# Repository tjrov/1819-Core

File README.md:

# 1819-Core
All software and hardware for 2018-19 season

## Software
### ControlStation
If you want to program something, the ControlStation is a great place to start.

So far, I've made abstract classes for sub-Panels of the GUI that control robot actuators
or read data from robot sensors. Serial comms are already taken care of. Just instantiate
one of the concrete subclasses and add it to the GUI controls.

The UpdateControls() methods are what draws the UI for each Device class. This method will run after the device is updated over serial.
New information will be available in the Data field of the class, and you can update the UI with that data.

TODO:
- Make UI look better (probably have the controls take up more of the screen and be laid out less haphazardly. Also maybe use win10 look and feel)
- Controller input
- Heading lock (override handheld controller values and control motors based on heading as compared to a desired heading)
- Depth lock
- Roll lock

It's recommended to use Visual Studio with the .NET and Windows Forms stuff installed for 
ControlStation development.

### autopilot-firmware

The autopilot-firmware and motorcontroller-firmware code is pretty much done. For development of firmware for the autopilot and motorcontroller, which are Arduino boards, install the Visual Micro plugin for Visual Studio. Upload the autopilot-firmware to a regular Arduino board connected to your computer over USB (comment out code that actually uses sensors and actuators since it won't work anyway), then start the ControlStation code and test out the UI.

### Uploading procedure

It's kinda complicated since we only have RS-485 (one twisted pair of wires) connecting the surface and ROV computers
1. You click upload in visual studio on the surface computer
2. The code gets compiled into a .hex file
3. The board.txt file (in the project directory) specifies a pre-upload command to run reset.bat (also in that directory)
4. reset.bat sends a command to the ROV: (hex) 42 83 01 03 02
5. On receiving this command, the autopilot-firmware (as well as the autopilot-setup code once it has finished running) will jump to the start of its bootloader code
6. reset.bat runs avrdude to upload the .hex file to the ROV

## Hardware

Electronics people can take a look at the autopilot board files. We'll also be making a
motorcontroller board that connects to the ROV's i2c bus. You can use Eagle with the Sparkfun Eagle part libraries installed to work on them.

Current autopilot revision features:
- Arduino Pro Mini
- RGB status LED
- RS485 interface
- Auto direction control of rs485 interface allows new firmware to be uploaded over the tether
- PCA-9615 differential I2C transceiver allows it to talk to the ROV data bus and access the motorcontroller board and the 6 ESC boards
- I2C Orientation sensor gives compass heading, pitch, and roll angles
- I2C Pressure sensor provides a depth reading

Motorcontroller current features:
- Arduino Pro Mini
- RGB status led
- PCA-9615 differential I2C transceiver (connects to the ROV i2c bus)
See the autopilot board schematic for how to wire the I2C circuits, since they
are the same on that board.
- Bus termination (see autopilot board schematic)
- 3x DRV8871 motor drivers. (wired as they are on the adafruit breakouts)

Motorcontroller planned additional features (need to be drawn in schematic and board files):
- I2C device that can generate PWM control signals for at least six ESCs (PCA-9685, perhaps)
- MOSFET switches (1-2Amp, at least 2 or 3 of them) controlled by these PWM signals

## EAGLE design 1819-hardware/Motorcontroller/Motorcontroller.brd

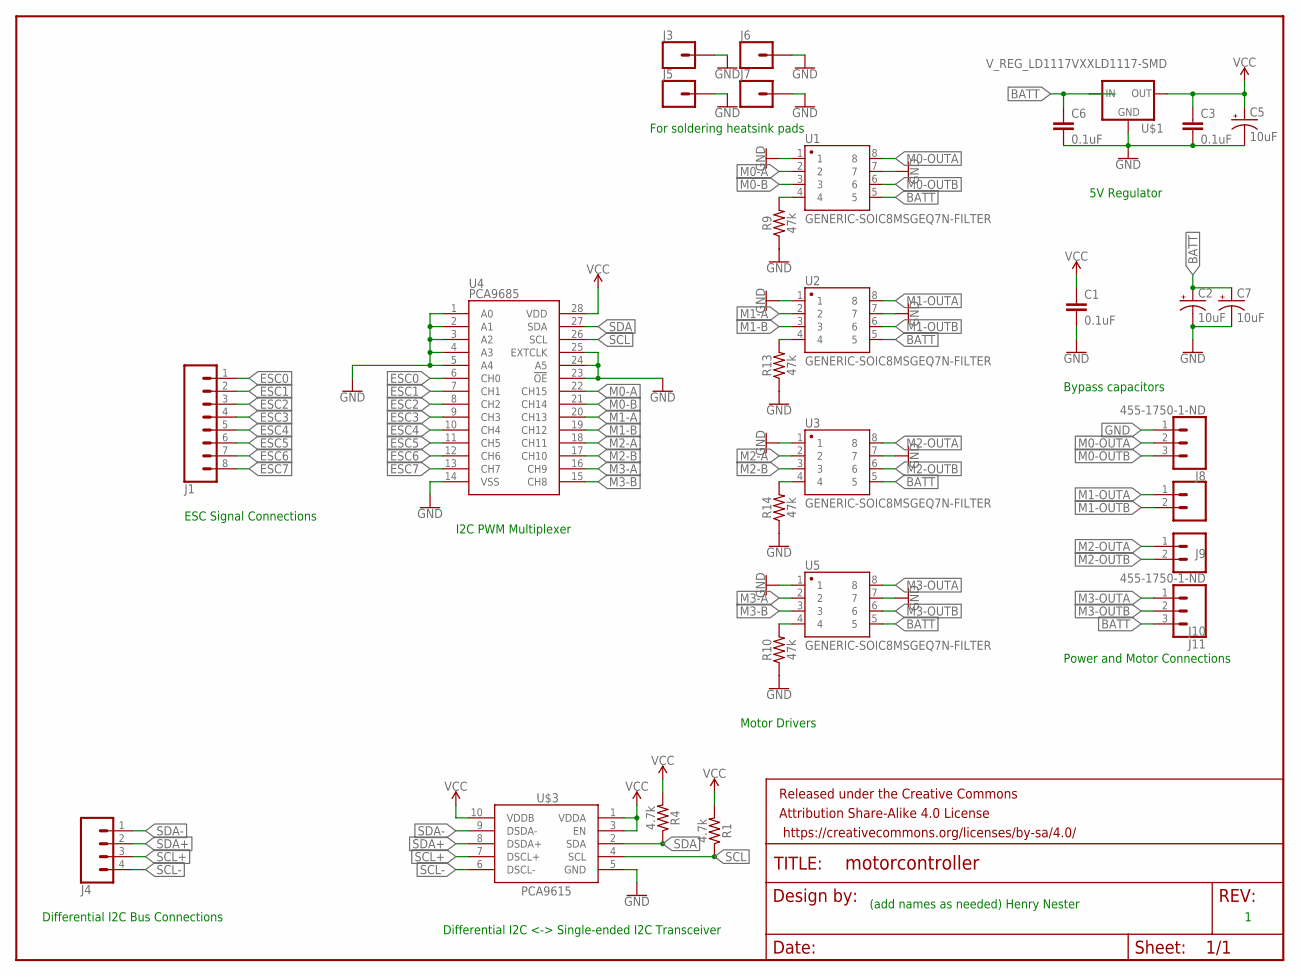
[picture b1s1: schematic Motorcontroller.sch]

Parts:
C1, C3, C6: 0.1uF; 0603
C2, C5, C7: 10uF; CPOL-RADIAL-2.5MM-5MM
FRAME1: FRAME-LETTERNO_PACKAGE; DUMMY
J1: CONN_08"; 1X08
J3, J5, J6, J7: CONN_01PTH_NO_SILK_YES_STOP; 1X01_NO_SILK
J4: CONN_04; 1X04
J8, J11: 455-1750-1-ND; 1X03
J9, J10: CONN_02; 1X02
R1, R4: 4.7k; 0603
R9, R10, R13, R14: 47k; 0603
U1, U2, U3, U5: GENERIC-SOIC8MSGEQ7N-FILTER; SO08
U4: PCA9685; TSSOP-28_4MM
U$1: V_REG_LD1117VXXLD1117-SMD; SOT223
U$3: PCA9615; TSSOP10

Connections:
BATT: C2.1 (+), C6.1, C7.1 (+), J11.3, U1.5, U2.5, U3.5, U5.5, U$1.3 (IN)
ESC0: J1.1, U4.6 (CH0)
ESC1: J1.2, U4.7 (CH1)
ESC2: J1.3, U4.8 (CH2)
ESC3: J1.4, U4.9 (CH3)
ESC4: J1.5, U4.10 (CH4)
ESC5: J1.6, U4.11 (CH5)
ESC6: J1.7, U4.12 (CH6)
ESC7: J1.8, U4.13 (CH7)
GND: C1.2, C2.2 (-), C3.2, C5.2 (-), C6.2, C7.2 (-), J3.1, J5.1, J6.1, J7.1, J8.1, R9.1, R10.1, R13.1, R14.1, U1.1, U1.7, U2.1, U2.7, U3.1, U3.7, U4.1 (A0), U4.2 (A1), U4.3 (A2), U4.4 (A3), U4.5 (A4), U4.14 (VSS), U4.23 (!OE), U4.24 (A5), U4.25 (EXTCLK), U5.1, U5.7, U$1.1 (GND), U$3.5 (GND)
M0-A: U1.2, U4.22 (CH15)
M0-B: U1.3, U4.21 (CH14)
M0-OUTA: J8.2, U1.8
M0-OUTB: J8.3, U1.6
M1-A: U2.2, U4.20 (CH13)
M1-B: U2.3, U4.19 (CH12)
M1-OUTA: J9.1, U2.8
M1-OUTB: J9.2, U2.6
M2-A: U3.2, U4.18 (CH11)
M2-B: U3.3, U4.17 (CH10)
M2-OUTA: J10.1, U3.8
M2-OUTB: J10.2, U3.6
M3-A: U4.16 (CH9), U5.2
M3-B: U4.15 (CH8), U5.3
M3-OUTA: J11.1, U5.8
M3-OUTB: J11.2, U5.6
unnamed: R13.2, U2.4
unnamed: R14.2, U3.4
unnamed: R10.2, U5.4
unnamed: R9.2, U1.4
SCL: R1.1, U4.26 (SCL), U$3.4 (SCL)
SCL+: J4.3, U$3.7 (DSCL+)
SCL-: J4.4, U$3.6 (DSCL-)
SDA: R4.1, U4.27 (SDA), U$3.2 (SDA)
SDA+: J4.2, U$3.8 (DSDA+)
SDA-: J4.1, U$3.9 (DSDA-)
VCC: C1.1, C3.1, C5.1 (+), R1.2, R4.2, U4.28 (VDD), U$1.2 (OUT), U$3.1 (VDDA), U$3.3 (EN), U$3.10 (VDDB)

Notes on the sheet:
(add names as needed) Henry Nester
5V Regulator
Power and Motor Connections
Bypass capacitors
I2C PWM Multiplexer
Motor Drivers
ESC Signal Connections
Differential I2C <-> Single-ended I2C Transceiver
Differential I2C Bus Connections
For soldering heatsink pads

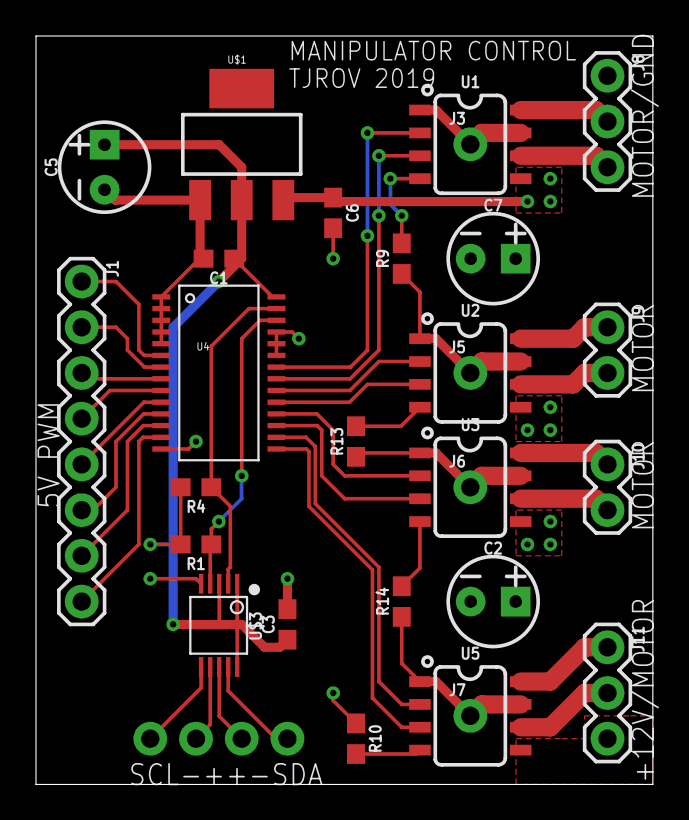
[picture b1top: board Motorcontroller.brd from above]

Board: 2 copper layers, 34.3 x 41.6 mm, 30 parts (1 on the bottom side), 37 nets.

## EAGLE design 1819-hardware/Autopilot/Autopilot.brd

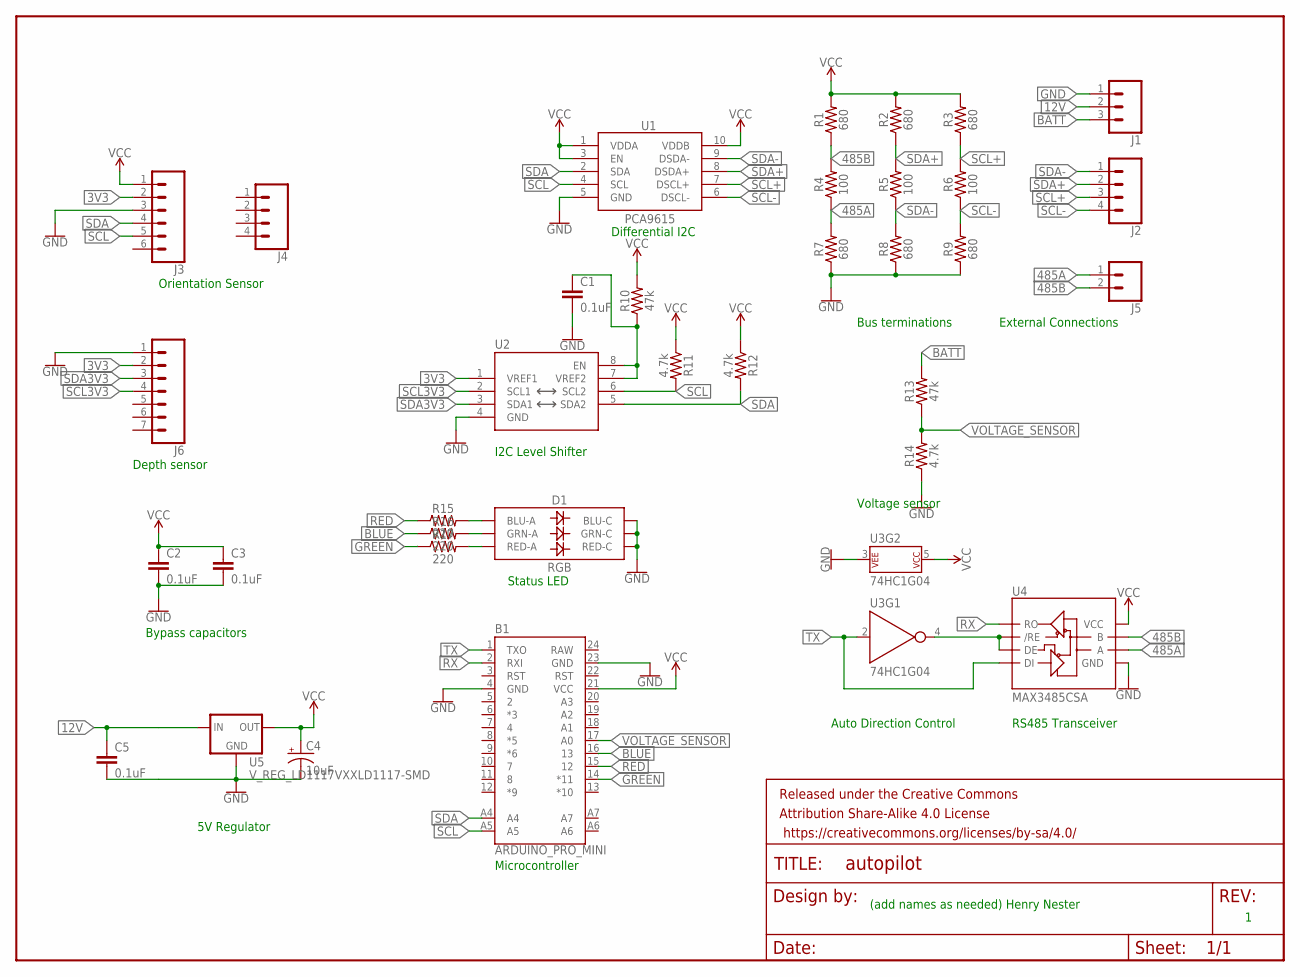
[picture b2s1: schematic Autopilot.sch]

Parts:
B1: ARDUINO_PRO_MINI
C1, C2, C3, C5: 0.1uF; 0603
C4: 10uF; CPOL-RADIAL-2.5MM-5MM
D1: RGB; PLCC-6-LED
FRAME1: FRAME-LETTERNO_PACKAGE; DUMMY
J1: CONN_03LONGPADS; 1X03_LONGPADS
J2: CONN_04; 1X04
J3: CONN_06NO_SILK_FEMALE_PTH; 1X06_NO_SILK
J4: CONN_041X04_NO_SILK; 1X04_NO_SILK
J5: CONN_02; 1X02
J6: CONN_07NO_SILK; 1X07_NO_SILK
R1, R2, R3, R7, R8, R9: 680; 0603
R4, R5, R6: 100; 0603
R10, R13: 47k; 0603
R11, R12, R14: 4.7k; 0603
R15, R16, R17: 220; 0603
U1: PCA9615; TSSOP10
U2: PCA9306MSOP-8; MSOP8
U3: 74HC1G04; SOT353
U4: MAX3485CSA; SO08
U5: V_REG_LD1117VXXLD1117-SMD; SOT223

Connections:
3V3: J3.2, J6.2, U2.1 (VREF1)
12V: C5.1, J1.2, U5.3 (IN)
485A: J5.1, R4.1, R7.2, U4.6 (A)
485B: J5.2, R1.1, R4.2, U4.7 (B)
BATT: J1.3, R13.2
BLUE: B1.16 (13), R16.1
GND: B1.4 (GND), B1.23 (GND), C1.2, C2.2, C3.2, C4.2 (-), C5.2, D1.CB (BLU-C), D1.CG (GRN-C), D1.CR (RED-C), J1.1, J3.3, J6.1, R7.1, R8.1, R9.1, R14.1, U1.5 (GND), U2.4 (GND), U3.3 (P$V-), U4.5 (GND), U5.1 (GND)
GREEN: B1.14 (*11), R17.1
unnamed: U3.4 (Y), U4.2 (/RE), U4.3 (DE)
unnamed: D1.AB (BLU-A), R15.2
unnamed: D1.AG (GRN-A), R16.2
unnamed: D1.AR (RED-A), R17.2
unnamed: C1.1, R10.1, U2.7 (VREF2), U2.8 (EN)
RAW: B1.24 (RAW)
RED: B1.15 (12), R15.1
RX: B1.2 (RXI), U4.1 (RO)
SCL: B1.A5, J3.5, R11.2, U1.4 (SCL), U2.6 (SCL2)
SCL3V3: J6.4, U2.2 (SCL1)
SCL+: J2.3, R3.1, R6.2, U1.7 (DSCL+)
SCL-: J2.4, R6.1, R9.2, U1.6 (DSCL-)
SDA: B1.A4, J3.4, R12.2, U1.2 (SDA), U2.5 (SDA2)
SDA3V3: J6.3, U2.3 (SDA1)
SDA+: J2.2, R2.1, R5.2, U1.8 (DSDA+)
SDA-: J2.1, R5.1, R8.2, U1.9 (DSDA-)
TX: B1.1 (TXO), U3.2 (A), U4.4 (DI)
VCC: B1.21 (VCC), C2.1, C3.1, C4.1 (+), J3.1, R1.2, R2.2, R3.2, R10.2, R11.1, R12.1, U1.1 (VDDA), U1.3 (EN), U1.10 (VDDB), U3.5 (P$V+), U4.8 (VCC), U5.2 (OUT)
VOLTAGE_SENSOR: B1.17 (A0), R13.1, R14.2

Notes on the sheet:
(add names as needed) Henry Nester
Orientation Sensor
Differential I2C
I2C Level Shifter
RS485 Transceiver
Auto Direction Control
5V Regulator
Microcontroller
External Connections
Status LED
Bus terminations
Bypass capacitors
Voltage sensor
Depth sensor

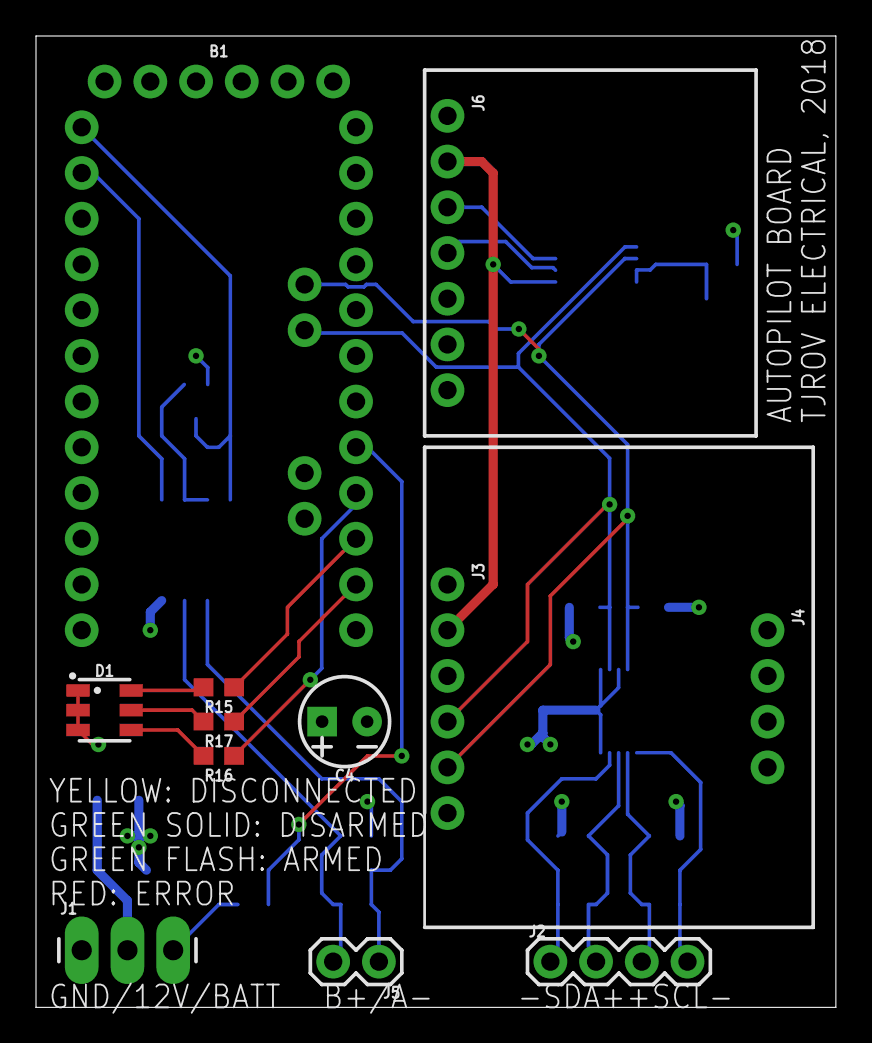
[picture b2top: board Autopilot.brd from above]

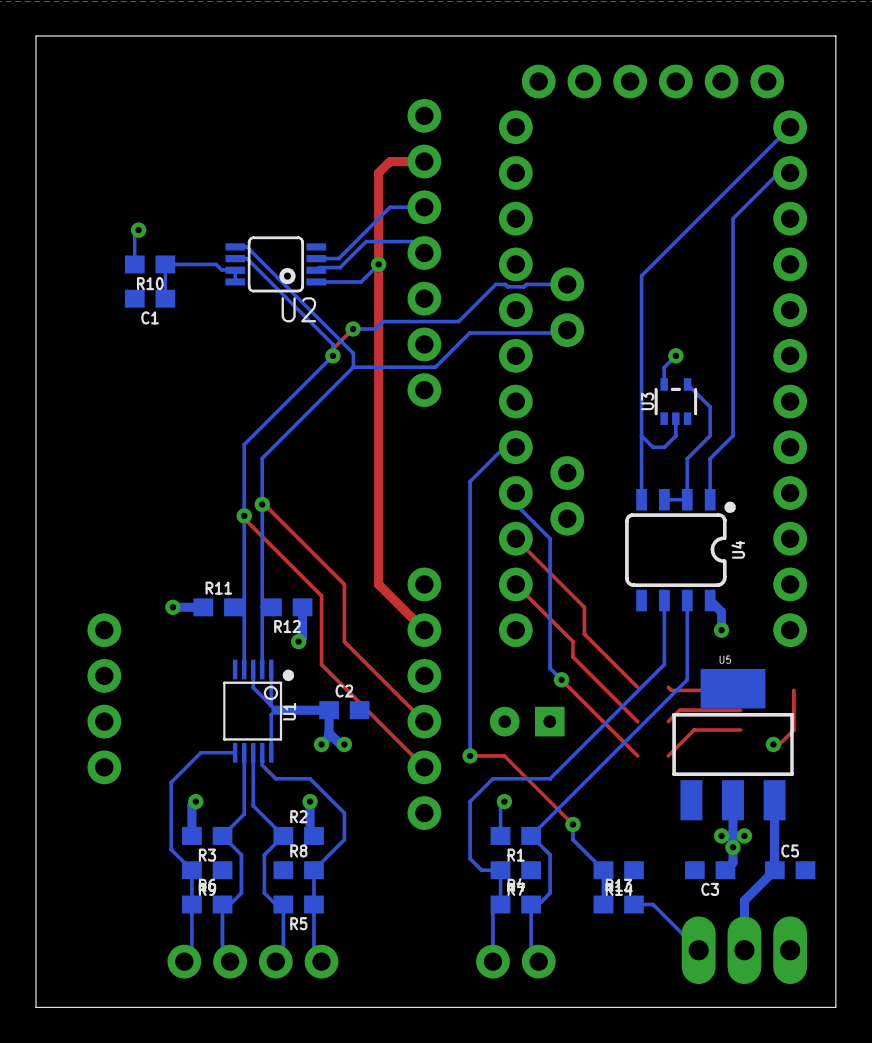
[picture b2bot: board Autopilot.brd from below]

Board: 2 copper layers, 44.4 x 54.0 mm, 36 parts (23 on the bottom side), 26 nets.

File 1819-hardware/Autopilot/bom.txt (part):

Partlist exported from C:/Users/Henry/source/repos/1819-Core/1819-hardware/Autopilot/Autopilot.sch at 9/2/2018 9:28 AM

Part   Value                     Device                          Package               Description                                                                                                     DESIGNER PROD_ID    VALUE       VERSION
B1     ARDUINO_PRO_MINI          ARDUINO_PRO_MINI                ARDUINO_PRO_MINI      SparkFun Pro Mini                                                                                                                                      
C1     0.1uF                     0.1UF-0603-25V-(+80/-20%)       0603                  0.1µF ceramic capacitors                                                                                                 CAP-00810  0.1uF              
C2     0.1uF                     0.1UF-0603-25V-(+80/-20%)       0603                  0.1µF ceramic capacitors                                                                                                 CAP-00810  0.1uF              
C3     0.1uF                     0.1UF-0603-25V-(+80/-20%)       0603                  0.1µF ceramic capacitors                                                                                                 CAP-00810  0.1uF              
C4     10uF                      10UF-POLAR-RADIAL-2.5MM-25V-20% CPOL-RADIAL-2.5MM-5MM 10.0µF polarized capacitors                                                                                              CAP-08440  10uF               
C5     0.1uF                     0.1UF-0603-25V-(+80/-20%)       0603                  0.1µF ceramic capacitors                                                                                                 CAP-00810  0.1uF              
D1     RGB                       LED-RGBPLCC-6                   PLCC-6-LED            LED-RGB                                                                                                                  DIO-12113  RGB                
FRAME1 FRAME-LETTERNO_PACKAGE    FRAME-LETTERNO_PACKAGE          DUMMY                 Schematic Frame - Letter                                                                                        Nobody                          v01    
J1                               CONN_03LONGPADS                 1X03_LONGPADS         Multi connection point. Often used as Generic Header-pin footprint for 0.1 inch spaced/style header connections                                        
J2                               CONN_04                         1X04                  Multi connection point. Often used as Generic Header-pin footprint for 0.1 inch spaced/style header connections          CONN-09696                    
J3                               CONN_06NO_SILK_FEMALE_PTH       1X06_NO_SILK          Multi connection point. Often used as Generic Header-pin footprint for 0.1 inch spaced/style header connections          CONN-08437                    
J4                               CONN_041X04_NO_SILK             1X04_NO_SILK          Multi connection point. Often used as Generic Header-pin footprint for 0.1 inch spaced/style header connections          CONN-09696                    
J5                               CONN_02                         1X02                  Multi connection point. Often used as Generic Header-pin footprint for 0.1 inch spaced/style header connections                                        
J6                               CONN_07NO_SILK                  1X07_NO_SILK          Multi connection point. Often used as Generic Header-pin footprint for 0.1 inch spaced/style header connections                                        
R1     680                       680OHM-0603-1/10W-5%            0603                  680Ω resistor                                                                                                            RES-09333  680                
R2     680                       680OHM-0603-1/10W-5%            0603                  680Ω resistor                                                                                                            RES-09333  680                
R3     680                       680OHM-0603-1/10W-5%            0603                  680Ω resistor                                                                                                            RES-09333  680                
R4     100                       100OHM-0603-1/4W-5%             0603                  100Ω resistor                                                                                                            RES-12438  100                
R5     100                       100OHM-0603-1/4W-5%             0603                  100Ω resistor                                                                                                            RES-12438  100                
R6     100                       100OHM-0603-1/4W-5%             0603                  100Ω resistor                                                                                                            RES-12438  100                
R7     680                       680OHM-0603-1/10W-5%            0603                  680Ω resistor                                                                                                            RES-09333  680                
R8     680                       680OHM-0603-1/10W-5%            0603                  680Ω resistor                                                                                                            RES-09333  680                
R9     680                       680OHM-0603-1/10W-5%            0603                  680Ω resistor                                                                                                            RES-09333  680                
R10    47k                       100KOHM-0603-1/10W-1%           0603                  100kΩ resistor                                                                                                           RES-07828  100k               
R11    4.7k                      4.7KOHM-0603-1/10W-1%           0603                  4.7kΩ resistor                                                                                                           RES-07857  4.7k               
R12    4.7k                      4.7KOHM-0603-1/10W-1%           0603                  4.7kΩ resistor                                                                                                           RES-07857  4.7k               
R13    47k                       100KOHM-0603-1/10W-1%           0603                  100kΩ resistor                                                                                                           RES-07828  100k               
R14    4.7k                      4.7KOHM-0603-1/10W-1%           0603                  4.7kΩ resistor                                                                                                           RES-07857  4.7k               
R15    220                       220OHM-0603-1/10W-1%            0603                  220Ω resistor                                                                                                            RES-07861  220                
R16    220                       220OHM-0603-1/10W-1%            0603                  220Ω resistor                                                                                                            RES-07861  220                
R17    220                       220OHM-0603-1/10W-1%            0603                  220Ω resistor                                                                                                            RES-07861  220                
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
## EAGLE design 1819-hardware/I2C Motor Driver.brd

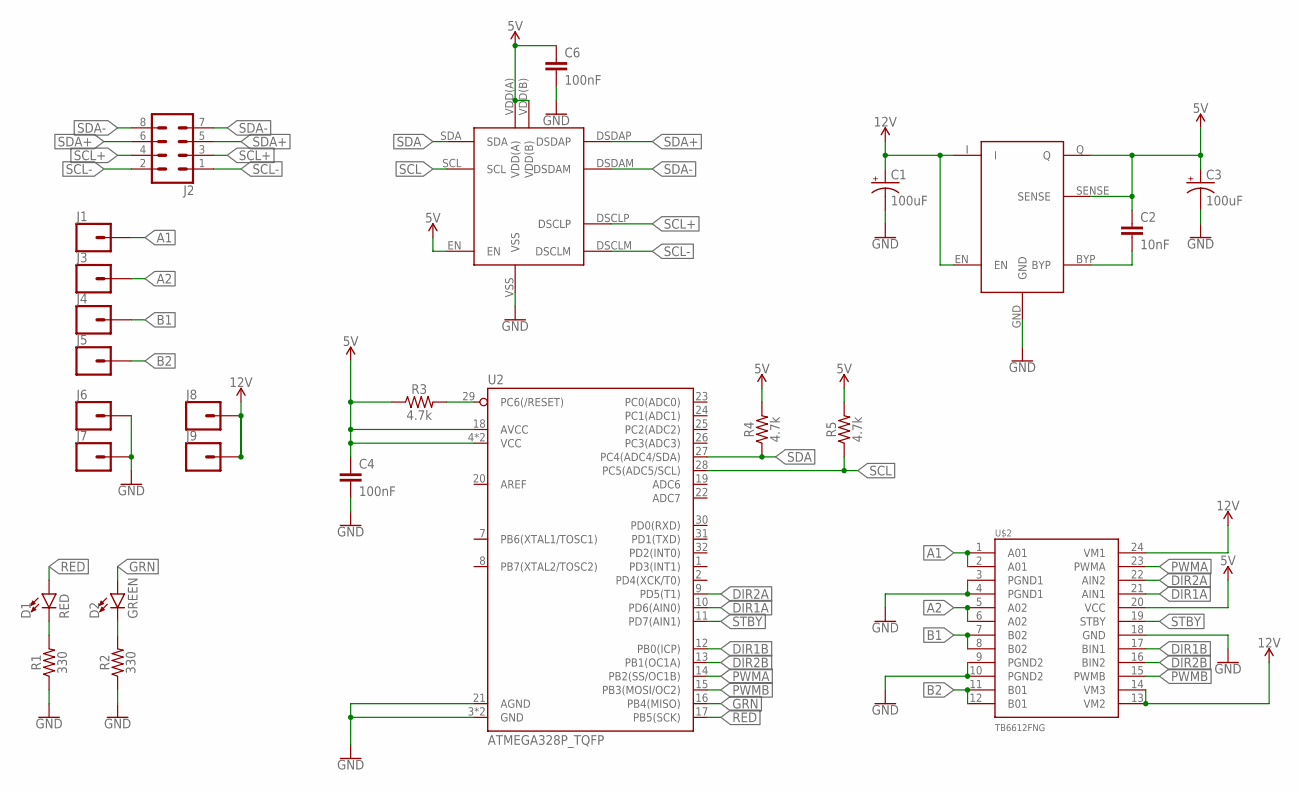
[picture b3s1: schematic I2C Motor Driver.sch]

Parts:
C1, C3: 100uF; CPOL-RADIAL-2.5MM-6.5MM
C2: 10nF; 0603
C4, C6: 100nF; 0603
D1: RED; LED-0603
D2: GREEN; LED-0603
J1, J3, J4, J5, J6, J7, J8, J9: CONN_01PTH_2MM; 1X01_2MM
J2: CONN_04X2; 2X4
R1, R2: 330; 0603
R3, R4, R5: 4.7k; 0603
U1: TLS205B0
U2: ATMEGA328P_TQFP; TQFP32-08
U$1: PCA9615
U$2: TB6612FNG; SSOP24

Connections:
5V: C2.1, C3.1 (+), C4.1, C6.1, R3.1, R4.2, R5.2, U1.Q, U1.SENSE, U2.4 (VCC), U2.6 (VCC), U2.18 (AVCC), U$1.EN, U$1.VDD(A), U$1.VDD(B), U$2.20 (VCC)
12V: C1.1 (+), J8.1, J9.1, U1.EN, U1.I, U$2.13 (VM2), U$2.14 (VM3), U$2.24 (VM1)
A1: J1.1, U$2.1 (A01), U$2.2 (A01)
A2: J3.1, U$2.5 (A02), U$2.6 (A02)
B1: J4.1, U$2.7 (B02), U$2.8 (B02)
B2: J5.1, U$2.11 (B01), U$2.12 (B01)
DIR1A: U2.10 (PD6(AIN0)), U$2.21 (AIN1)
DIR1B: U2.12 (PB0(ICP)), U$2.17 (BIN1)
DIR2A: U2.9 (PD5(T1)), U$2.22 (AIN2)
DIR2B: U2.13 (PB1(OC1A)), U$2.16 (BIN2)
GND: C1.2 (-), C3.2 (-), C4.2, C6.2, J6.1, J7.1, R1.1, R2.1, U1.GND, U2.3 (GND), U2.5 (GND), U2.21 (AGND), U$1.VSS, U$2.3 (PGND1), U$2.4 (PGND1), U$2.9 (PGND2), U$2.10 (PGND2), U$2.18 (GND)
GRN: D2.A, U2.16 (PB4(MISO))
unnamed: C2.2, U1.BYP
unnamed: D2.C, R2.2
unnamed: D1.C, R1.2
unnamed: R3.2, U2.29 (PC6(/RESET))
PWMA: U2.14 (PB2(SS/OC1B)), U$2.23 (PWMA)
PWMB: U2.15 (PB3(MOSI/OC2)), U$2.15 (PWMB)
RED: D1.A, U2.17 (PB5(SCK))
SCL: R5.1, U2.28 (PC5(ADC5/SCL)), U$1.SCL
SCL+: J2.3, J2.4, U$1.DSCLP
SCL-: J2.1, J2.2, U$1.DSCLM
SDA: R4.1, U2.27 (PC4(ADC4/SDA)), U$1.SDA
SDA+: J2.5, J2.6, U$1.DSDAP
SDA-: J2.7, J2.8, U$1.DSDAM
STBY: U2.11 (PD7(AIN1)), U$2.19 (STBY)

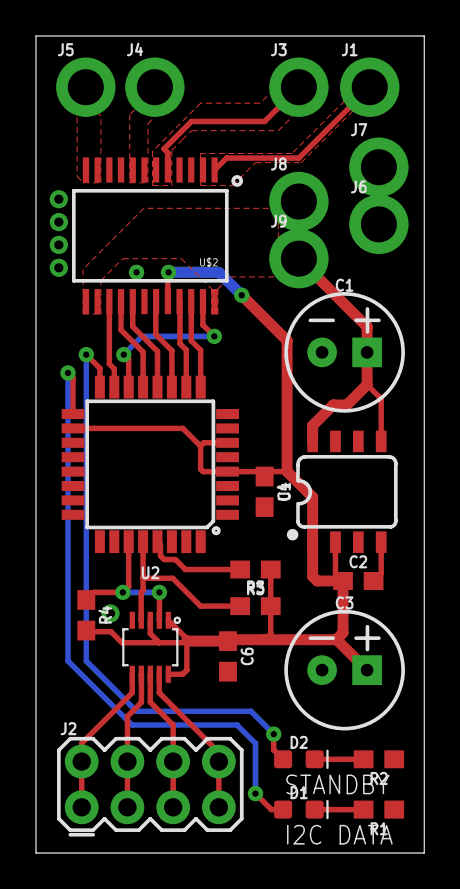
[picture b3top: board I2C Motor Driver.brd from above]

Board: 2 copper layers, 21.6 x 45.4 mm, 25 parts (0 on the bottom side), 26 nets.

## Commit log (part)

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2018-07-07 moved in lib files (.h & .cpp)
2018-07-07 fixed visual studio retardation with files
2018-07-07 added serial communication functions
2018-07-07 rename to 1819-software
2018-07-16 name change
    THE NAME GAMEEEEE
    JUDY!
    JUDY JUDY JUBUDY
    BANANANA BAFUDY
2018-07-17 Fixing Errors
    The solution builds now (Though will skip the other two Henry specified)
2018-08-04 fixed up GUI
    lol what
2018-08-09 add code
2018-08-09 combined my new code
2018-08-09 fix Arduino bug; add depth and tool support
    request messages that contained no data left the arduino stuck waiting for a data section
    added Tools and Depth classes
2018-08-09 methods for interfacing with sensors, escs, manipulators on ROV
2018-08-10 dont forget to add slimdx as a reference
2018-08-11 better, one error now
2018-08-11 We get this exception... Fixed all errors.
    System.IO.FileLoadException: 'Mixed mode assembly is built against version 'v2.0.50727' of the runtime and cannot be loaded in the 4.0 runtime without additional configuration information.'
2018-08-11 comment explanation
2018-08-11 reset script added
2018-08-12 motorcontroller board code & compatibility in autopilot board code
2018-08-12 subpanels now render
2018-08-12 motor brakes instead of coasts, fix i2c checksums
2018-08-12 StatusActuator graphics implemented
2018-08-13 Revert "Merge branch 'master' of https://github.com/tjrov/1819-Core"
    This reverts commit bfdea0ab5491b7438a186bc3d3f932f2a784947c, reversing
    changes made to eb7a581f4c45772150ac41e0f4cf37380e2fd86d.
2018-08-13 Revert "wtf"
    This reverts commit eb7a581f4c45772150ac41e0f4cf37380e2fd86d.
2018-08-13 multithread comms
2018-08-13 DevicePanel added (display class for Sensors/Actuators)
2018-08-13 added GUI to StatusSensor/Actuator.
2018-08-13 latest versiom
2018-08-14 working!
2018-08-14 fix status panel
2018-08-15 whew. good and solid
2018-08-15 new autopilot-firmware
2018-08-15 Revert "Merge branch 'master' of https://github.com/tjrov/1819-Core"
    This reverts commit 6b2372429231f09f6513fa531bcf1b22eeda4953, reversing
    changes made to 46dec0436ab7a38d72fc954168becce475bd38a5.
2018-08-15 receive timeout added
2018-08-15 added BarGraphLabel class
2018-08-15 fixed BarGraph
2018-08-15 working on axis remap to make attitude indicator work
2018-08-16 attitude indicator works
2018-08-16 add esc controls
2018-08-16 fixed reboot loop
2018-08-16 added autopilot board files
2018-08-16 toolpanel
2018-08-16 added depthindicator
2018-08-16 added compass
2018-08-16 clean up compass code
2018-08-16 markedheading property for compass allows to display the heading lock angle
2018-08-17 bad cahnges
2018-08-17 added checkI2C(address)
2018-08-17 added rov renders to resources
2018-08-17 error enum values can be combined
2018-08-17 rov renders as gui
2018-08-17 added heading and attitude indicators
2018-08-17 generic device extends control
2018-08-17 ui changes
2018-08-17 ui work
2018-08-17 more ui work
2018-08-17 fixed firmware bug
2018-08-18 worked on ui
2018-08-18 port and baud rate drop down menus
2018-08-19 added esc inversion, setup utility firmware
2018-08-19 updated Autopilot board files
2018-08-20 serial port configurable in app settings
2018-08-20 added manipulator motor test
2018-08-21 controllers work now
2018-08-21 routing of motorcontroller board files
2018-08-21 more board routing
2018-08-22 Uploading over rs485 works
2018-08-23 more controller
2018-08-24 i don't know
2018-08-26 working on motorcontroller board files
2018-08-26 worked on routing
2018-08-27 the arduino was upside down
2018-08-27 stuff
2018-09-01 working on boards
2018-09-02 Ordered parts
2018-09-03 serial port logging and cleaned up code
2018-09-03 log saves to .exe directory
2018-09-03 bad changes
2018-09-03 Revert "bad changes"
    This reverts commit bfb741ae3c4203d47f84c6b6031aebf824e639b9.
2018-09-03 added lock display to indicators
2018-09-07 updated boards
    700mil spacing on BNO055
    changed PCA9306 package to MSOP8
2018-09-07 more chngs
2018-09-07 test faster baud rate with new terminations
2018-09-08 worked on boards
2018-09-12 working on latest hardware
2018-09-15 close comms thread to prevent crashing on form close
2018-09-15 enable/disable panels on connect/disconnect
2018-09-15 bug really is fixed now.
2018-09-15 blah
2018-09-15 Revert "blah"
    This reverts commit b1181d7048ba8046d9914c7d95373fd2738d8a74.
2018-09-15 Revert "got that bug the foh"
    This reverts commit 601e3be7af3d8458a6810ab124a50ccfeeea229e.
2018-09-15 Revert "enable/disable panels on connect/disconnect"
    This reverts commit 0d815958b92d4a4fbda0504ab9e1b606a1564cc2.
2018-09-15 Revert "close comms thread to prevent crashing on form close"
    This reverts commit 658eea6ff7444f3cc500fe72bebd8ad9dccba428.
2018-09-15 Revert "bh"
    This reverts commit 9a01385e8d953308ed5dfa087e9342c15df98309.
2018-09-15 Revert "Revert "enable/disable panels on connect/disconnect""
    This reverts commit 08b97820abe82fd9cd14fe374b0ff314734115da.
2018-09-15 Revert "Revert "bug really is fixed now.""
    This reverts commit cf659f52283e35ed2ff2e039bf45a7f2edaad847.
2018-09-15 Revert "Revert "got that bug the foh""
    This reverts commit d268d2d99085f5298c40e5eedcfa1c58fd93c296.
2018-09-15 idk why but moving linkActive = value down in the code fixed it
2018-09-15 fixed motorcontroller firmware
2018-09-15 Revert "ignore this"
    This reverts commit dcebcec30bbd8f54295638636b960e6fcf54ac23.
2018-09-15 Redistribution
    Communism.exe
2018-09-15 gui
    gui
2018-09-15 a
    a
2018-09-15 a
    a
2018-09-15 commit memen't
2018-09-15 images for resources
2018-09-15 final push for me
    final push of the day
2018-09-16 deleted unecessary resource files
2018-09-16 show exception dialog from serial
2018-09-16 updatecontrols remvoed from devices
2018-09-16 settings cancel button & can now only arm ROV while connected
2018-09-16 added menu strip up top
2018-09-16 dropdown menu works
2018-09-23 added arduino code to gui(18-19)
2018-09-23 moved files
2018-09-23 firmware error handling
2018-10-20 component positions done
2018-10-20 motorcontroller board
2018-10-20 more work on boards
2018-10-24 Added support for new ROV hardware for second team
2018-10-25 remade project to let Kevin open it hopefully
2018-10-25 firmware working
2018-10-25 Fixed Crashing Bug
    *Try catch added to BetterSerialPort.cs method Open() to catch unhandled port exception
    *Changed title text on main window from "form1" to "TJROV - GUI"
2018-10-25 Implemented Fullscreen
    *Added GoFulscreen method to MainForm.cs
    *Added exit button to close the application while in fullscreen.
2018-10-30 deprecated 1819-software
2018-10-31 fixed indicators/added reset button
2018-10-31 test change
2018-11-20 Revert "autopilot-firmware: fixed lockup during ESC undervoltage"
    This reverts commit e0084f3473392965348a4576d3a924ece87e4535.
2018-11-28 Hi my name is Edward Lee
2018-11-28 added my name
2018-12-01 Revert "commit"
    This reverts commit 4bcb39d2aef03651ea29089e80ad9ded419dc7c4.
2018-12-01 update
    -adding support for controllers
    -push 1/3
2018-12-01 update
    -adding support for controllers
    -push 3/3
    -this api that I used is bad, will rewrite later with default windows api instead of slimdx
2018-12-01 update
    added connection button for controller
2019-01-03 worked on board
2019-01-15 Revert "bad changes"
    This reverts commit 0c4913564e4813e8fcba2956afc58c2d3b22559f.
2019-01-19 fixed esc and tool outputs on arduino
2019-01-19 ok now
2019-01-19 added Controller.cs
2019-01-20 fixed pca9685 reset messing up pwm outputs
2019-01-21 fixed serial not restarting after a communication glitch
2019-01-21 added ROV class in Vehicle folder
2019-01-22 added turn, strafe, depth lock, attitude assist logic
2019-01-22 display all controller buttons and axes in top right
2019-01-23 The best update yet
    everything works now
2019-01-24 fix problems
2019-01-26 Mainform.cs
    Fixed bugs from DepthLock and edited designer
2019-01-26 Added big gay
2019-01-26 Mainform.cs
    progress bar stuff
2019-01-26 yeet finished the things
    my chungus is DIVERGENT
2019-01-26 Mainform.cs
    stuff with actuators for claw
2019-01-26 Shape Checker CV
2019-01-26 added one thing that i had to commit
2019-01-29 celebrate good times come on
    we evaded the magic smoke on the electronics with some sketchy wiring shhh....
    changed the code to account for changes
2019-01-29 propulsionactuator sends motor speeds as 8-bit instead of 16-bit numbers
2019-01-29 tools are working correctly
2019-01-30 removed serial logging since thread conflict happens
2019-02-01 Update
    Fixed bugs that Henry Described and also made the GUI look a lot nice, should be 100% ready for testing with ROV now.
2019-02-01 error dialog
2019-02-01 arduino restarts i2c after a failure
2019-02-02 Mainfom.cs, ROV.cs
    changed range -100 to 100 to -50 to 50
2019-02-02 added volume calculation
2019-02-02 implemented aforge code
    added the dlls
    added some needed methods
    still have to cod ethe part where you get the image
2019-02-04 Shape Detection
    This program can detect the shapes from an image from an external camera. But the parameters need to be adjusted based on the actual camera in the ROV and how the image looks underwater.
2019-02-06 SerialCommunication.cs
    fixed error with ocmmunication
2019-02-09 added buttons for front, left, right, back preference
2019-02-09 made logic for directional change
2019-02-10 added button onclick listeners
2019-02-10 changes directionPref value
2019-02-10 added parity stuff
2019-02-12 fix arduino code bug
2019-02-16 added counting shape
2019-02-16 yases
2019-02-16 dont delet code pls
2019-02-24 dun dunm dun
2019-03-02 fdsfsd can get video from oem capture sTICK
    do you know the wae
2019-03-02 oops
2019-03-18 emgu
2019-03-19 mini commit
2019-03-20 small change
2019-03-20 changed ESC PWM values
2019-03-20 K
    K
2019-03-21 GUI update
2019-03-21 controller gui
2019-03-21 controller gui code
2019-03-22 name changes
2019-03-22 cv
    comparing EmguCV and AForge.NET
2019-03-23 testing something
2019-03-23 fixed something
2019-03-24 fixed typo, testing servo
2019-03-25 logic gates with perceptrons
2019-03-29 compile errors fixed
2019-03-30 cv gui update
2019-04-04 added images
2019-04-05 test
2019-04-05 bug fix
2019-04-12 small update
2019-04-12 mirror of master
2019-04-12 mini rov
2019-04-13 Add files via upload
    CV code that actually works. Uses command line args as input.
    Usage: python shapeDetection.py <jpg image name but no .jpg at the end>
2019-04-13 fixed thruster directions/mapping
2019-04-18 added arduino i2c bridge code
2019-04-19 planning to use another i2c library, commit now to save changes
2019-04-19 autopilot-firmware now uses I2C-master library, which does not hang in bus faults
2019-04-19 UI Updates
2019-04-19 removed communications support in lieu of henrys solution
2019-04-19 f
    f
2019-04-27 MiniROV launch code for control station
2019-04-27 added miniROV launch to autopilot firmware PWM values need to be changed
2019-04-27 yeet
2019-04-27 changed camera type
2019-04-27 GUI
    fixed button discrepency
2019-04-27 GUI
    math bug and labels fixed
2019-04-28 Removed old servo debug
2019-04-28 fixed odd bug
2019-04-28 Removed mini rov launcher
2019-04-28 fixed another bug
2019-04-28 Servo debug + removed minirov in arduino
    connect rx from one arduino to another to use that com port for serial monitor
2019-04-29 servo update
2019-05-02 GUI Update
    -Fixed Crashing Bug when ROV isn't connected
    -Re-added the gyroscope indicator
    -Changed Baud Rate to 9600 in ROV and GUI code
2019-05-02 GUI Update
    -Deleted unused methods
    -Fixed CV Method
2019-05-02 GUI Update
    -Fixed Button Enabled Bug
2019-05-02 one place to define the pins/channels for ESCS
2019-05-02 GUI Update
    -Fixed Crash Error (Still needs to be reimplemented)
    -Fixed Altitude Sensor
2019-05-02 camera control switch
2019-05-03 Revert "camera control switch"
    This reverts commit 09ae34a587db551b5a2594b00085d2328c5b6da1.
2019-05-03 updated tilt power

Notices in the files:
parts and their libraries:
SparkFun-Boards: Licensing: Creative Commons ShareAlike 4.0 International - https://creativecommons.org/licenses/by-sa/4.0
SparkFun-Aesthetics: Released under the Creative Commons Attribution Share-Alike 4.0 License
SparkFun-Aesthetics: https://creativecommons.org/licenses/by-sa/4.0
